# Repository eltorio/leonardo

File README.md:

# Leonardo
Arduino Leonardo schematic ported to Kicad

# Star the project

**If you appreciate my work, please consider giving it a star! 🤩**

# Kicad 8
The design has been ported to Kicad 8.  
* DRC shows no error nor warning on PCB.
* All selected parts are easily availables.
* All parts contains 3 additional fields
    * Manufacturer containing the name of the manufacturer
    * Manufacturer_ref containing the part real reference
    * Digikey_ref containing a Digikey part number

NM, DNP parts are parts not mounted

# Why
Because I need to adapt the Leonardo design to include other functionalities my first work is to port the very good Arduino Leonardo rev3d to Kicad 6.  

# Crystal
16MHz Crystal is not yet selected…

# Schematic

# Board

The board is adapted and routed with the parts I have selected.  
Kicad 8 DRC check doesn't show any errors nor any warning.  
Component references are hidden by default to match the Arduino Leonardo silkscreen. If you need the references, use the [Hide References plugin](https://github.com/joelsa/kicad-hide-references-plugin) which can be easily installed via the Plugin and Content Manager.

# 3D Render

## Without component references

## With component references

# BOM
The [BOM](https://raw.githubusercontent.com/eltorio/leonardo/main/Leonardo_Rev3e.html) was automatically generated with [python/bom.py](https://github.com/eltorio/leonardo/blob/main/python/bom.py) add this script in the BOM dialog.  
The html BOM was converted to MarkDown with https://www.convertsimple.com/convert-html-to-markdown/   

[comment]: <> (generated from html bom with https://www.convertsimple.com/convert-html-to-markdown/)  
**Component Count: 56**

| Ref | Qnty | Value | Footprint | Datasheet | Manufacturer | Manufacturer_ref | Digikey_ref |
| --- | --- | --- | --- | --- | --- | --- | --- |
| C1, C2, C6, C9, C13, C22 | 6   | 100n | Leonardo_Rev3e:C0603-ROUND | [link](https://connect.kemet.com:7667/gateway/IntelliData-ComponentDocumentation/1.0/download/datasheet/C0603C104J4RACTU) | Kemet | C0603C104J4RAC7867 | [399-C0603C104J4RAC7867CT-ND](https://www.digikey.com/en/products?mpart=399-C0603C104J4RAC7867CT-ND) |
| C3, C4 | 2   | 22p | Leonardo_Rev3e:C0603-ROUND | [link](https://connect.kemet.com:7667/gateway/IntelliData-ComponentDocumentation/1.0/download/datasheet/C0603C220K5RAC7867) | Kemet | C0603C220K5RAC7867 | [399-14962-1-ND](https://www.digikey.com/en/products?mpart=399-14962-1-ND) |
| C5, C7, C11, C14 | 4   | 1uF | Leonardo_Rev3e:C0603-ROUND | [link](https://connect.kemet.com:7667/gateway/IntelliData-ComponentDocumentation/1.0/download/datasheet/C0603C105K4RAC7411) | Kemet | C0603C105K4RAC7411 | [399-C0603C105K4RAC7411CT-ND](https://www.digikey.com/en/products?mpart=399-C0603C105K4RAC7411CT-ND) |
| C8, C10, C12 | 3   | 10u | Leonardo\_Rev3d:SMC\_B | [link](https://api.kemet.com/component-edge/download/datasheet/T491B106M016AT.pdf) | Kemet | T491B106M016AT | [399-3708-1-ND](https://www.digikey.com/en/products?mpart=399-3708-1-ND) |
| D1  | 1   | M7  | Leonardo_Rev3e:SMB |     |     |     |     |
| D2  | 1   | 1N4148W-TP | Leonardo_Rev3e:MINIMELF | [link](https://www.mccsemi.com/pdf/Products/1N4148W(SOD-123).pdf) | MCC | 1N4148W-TP | [1N4148WTPMSCT-ND](https://www.digikey.com/en/products?mpart=1N4148WTPMSCT-ND) |
| D+0 | 1   | DNP | Leonardo_Rev3e:TP-1.00MM |     |     |     |     |
| D-0 | 1   | DNP | Leonardo_Rev3e:TP-1.00MM |     |     |     |     |
| EXTPOWER0 | 1   | POWERSUPPLY_DC21MMX | Leonardo\_Rev3d:POWERSUPPLY\_DC-21MM |     |     |     |     |
| F1  | 1   | MF-MSMF050-2 500mA | Leonardo_Rev3e:L1812 | [link](https://www.bourns.com/docs/product-datasheets/mf-msmf.pdf) | Bourns | MF-MSMF050-2 | [MF-MSMF050-2CT-ND](https://www.digikey.com/en/products?mpart=MF-MSMF050-2CT-ND) |
| FID1, FID2, FID3 | 3   | DNP | Leonardo_Rev3e:FD-1-1.5 |     |     |     |     |
| GND0 | 1   | DNP | Leonardo_Rev3e:TP-1.00MM |     |     |     |     |
| IC1 | 1   | REG1117-5 | Leonardo_Rev3e:SOT223 | [link](https://www.ti.com/lit/gpn/reg1117) | TI  | REG1117-5 | [REG1117-5-ND](https://www.digikey.com/en/products?mpart=REG1117-5-ND) |
| IC2 | 1   | LMV358IDGKR | Leonardo_Rev3e:MSOP08 | [link](https://www.ti.com/lit/gpn/lmv358) | TI  | 296-13455-1-ND | [LMV358IDGKR](https://www.digikey.com/en/products?mpart=LMV358IDGKR) |
| ICSP0 | 1   | ICSP | Leonardo_Rev3e:2X03 | [link](https://www.te.com/commerce/DocumentDelivery/DDEController?Action=srchrtrv&DocNm=146486&DocType=Customer+Drawing&DocLang=English) | TE  | 5-146486-3 | [A128860-ND](https://www.digikey.com/en/products?mpart=A128860-ND) |
| J1  | 1   | USBMICRO | Leonardo_Rev3e:10118194-0001LF | [link](https://www.amphenol-cs.com/media/wysiwyg/files/drawing/10118194.pdf) | Amphenol | 10118194-0001LF | [609-4618-1-ND](https://www.digikey.com/en/products?mpart=609-4618-1-ND) |
| J2, J3 | 2   | 8x1F-H8.5 | Leonardo_Rev3e:1X08 | [link](https://media.digikey.com/pdf/Data%20Sheets/Sullins%20PDFs/Female_Headers.100_DS.pdf) | Sullins | PPPC081LFBN-RC | [S7041-ND](https://www.digikey.com/en/products?mpart=S7041-ND) |
| J4  | 1   | 6x1F-H8.5 | Leonardo_Rev3e:1X06 | [link](https://media.digikey.com/pdf/Data%20Sheets/Sullins%20PDFs/Female_Headers.100_DS.pdf) | Sullins | PPPC061LFBN-RC | [S7039-ND](https://www.digikey.com/en/products?mpart=S7039-ND) |
| JP1 | 1   | 10x1F-H8.5 | Leonardo_Rev3e:1X10 | [link](https://media.digikey.com/pdf/Data%20Sheets/Sullins%20PDFs/Female_Headers.100_DS.pdf) | Sullins | PPPC101LFBN-RC | [S7043-ND](https://www.digikey.com/en/products?mpart=S7043-ND) |
| JP2 | 1   | OTG | Leonardo\_Rev3d:HEADER\_2_2.54 | [link](~) | Samtex | DW-02-07-T-S-200 | [SAM15134-ND](https://www.digikey.com/en/products?mpart=SAM15134-ND) |
| L0  | 1   | Yellow | Leonardo\_Rev3d:CHIPLED\_0805 | [link](https://optoelectronics.liteon.com/upload/download/DS22-2000-110/LTST-C171KSKT.pdf) | Lite-on | LTST-C171KSKT | [160-1428-1-ND](https://www.digikey.com/en/products?mpart=160-1428-1-ND) |
| L1, L2 | 2   | MH2029-300Y | Leonardo_Rev3e:0805 | [link](https://www.bourns.com/docs/Product-Datasheets/mh.pdf) | Bourns | MH2029-300Y | [MH2029-300YCT-ND](https://www.digikey.com/en/products?mpart=MH2029-300YCT-ND) |
| ON0 | 1   | Green | Leonardo\_Rev3d:CHIPLED\_0805 | [link](https://optoelectronics.liteon.com/upload/download/DS22-2000-110/LTST-C171KSKT.pdf) | Lite-on | LTST-C171KGKT | [160-1426-1-ND](https://www.digikey.com/en/products?mpart=160-1426-1-ND) |
| R1  | 1   | 1M  | Leonardo_Rev3e:R0603-ROUND | [link](https://www.bourns.com/docs/product-datasheets/cr.pdf?sfvrsn=574d41f6_14) | Bourns | CR0603-FX-1004ELF | [CR0603-FX-1004ELFCT-ND](https://www.digikey.com/en/products?mpart=CR0603-FX-1004ELFCT-ND) |
| R2, R3 | 2   | NM  | Leonardo_Rev3e:R0402 |     |     |     |     |
| R4  | 1   | 10K | Leonardo_Rev3e:R0603-ROUND | [link](https://www.bourns.com/docs/product-datasheets/cr.pdf?sfvrsn=574d41f6_14) | Bourns | CR0603-FX-1002ELF | [CR0603-FX-1002ELFCT-ND](https://www.digikey.com/en/products?mpart=CR0603-FX-1002ELFCT-ND) |
| RESET0 | 1   | TS07-667-30-BK-160-SMT-TR | Leonardo_Rev3e:TS07 | [link](https://www.cuidevices.com/product/resource/ts07.pdf) | CUI | TS07-667-30-BK-160-SMT-TR | [2223-TS07-667-30-BK-160-SMT-TRCT-ND](https://www.digikey.com/en/products?mpart=2223-TS07-667-30-BK-160-SMT-TRCT-ND) |
| RN1 | 1   | 10K | Leonardo_Rev3e:CAY16 | [link](https://www.bourns.com/docs/Product-Datasheets/CATCAY.pdf) | Bourns | CAY16-1002F4LF | [CAY16-1002F4LFCT-ND](https://www.digikey.com/en/products?mpart=CAY16-1002F4LFCT-ND) |
| RN2 | 1   | 1K  | Leonardo_Rev3e:CAY16 | [link](https://www.bourns.com/docs/Product-Datasheets/CATCAY.pdf) | Bourns | CAY16-1001F4LF | [CAY16-1001F4LFCT-ND](https://www.digikey.com/en/products?mpart=CAY16-1001F4LFCT-ND) |
| RN3 | 1   | 22R | Leonardo_Rev3e:CAY16 | [link](https://www.bourns.com/docs/Product-Datasheets/CATCAY.pdf) | Bourns | CAY16-22R0F4LF | [CAY16-22R0F4LFCT-ND](https://www.digikey.com/en/products?mpart=CAY16-22R0F4LFCT-ND) |
| RX0 | 1   | Yellow | Leonardo\_Rev3d:CHIPLED\_0805 | [link](https://optoelectronics.liteon.com/upload/download/DS22-2000-110/LTST-C171KSKT.pdf) | Lite-on | LTST-C171KSKT | [160-1426-1-ND](https://www.digikey.com/en/products?mpart=160-1426-1-ND) |
| T1  | 1   | FDN340P | Leonardo_Rev3e:SOT-23 | [link](https://media.digikey.com/pdf/Data%20Sheets/UTD%20Semi%20PDFs/UMW%20FDN340P.pdf) | UMW | FDN340P | [4518-FDN340PCT-ND](https://www.digikey.com/en/products?mpart=4518-FDN340PCT-ND) |
| TX0 | 1   | Yellow | Leonardo\_Rev3d:CHIPLED\_0805 | [link](https://optoelectronics.liteon.com/upload/download/DS22-2000-110/LTST-C171KSKT.pdf) | Lite-on | LTST-C171KSKT | [160-1426-1-ND](https://www.digikey.com/en/products?mpart=160-1426-1-ND) |
| U1  | 1   | ATMEGA32U4-XUMU | Leonardo_Rev3e:QFN44ML7X7 | [link](http://ww1.microchip.com/downloads/en/DeviceDoc/Atmel-7766-8-bit-AVR-ATmega16U4-32U4_Summary.pdf) | Microchip | ATMEGA32U4-MU | [ATMEGA32U4-MU-ND](https://www.digikey.com/en/products?mpart=ATMEGA32U4-MU-ND) |
| U2  | 1   | ATMEGA32U4-XUAU | Leonardo_Rev3e:TQFP44-PAD | [link](http://ww1.microchip.com/downloads/en/DeviceDoc/Atmel-7766-8-bit-AVR-ATmega16U4-32U4_Summary.pdf) | Microchip | ATMEGA32U4-AU | [ATMEGA32U4-AU-ND](https://www.digikey.com/en/products?mpart=ATMEGA32U4-AU-ND) |
| U3  | 1   | LP2985-33DBVR | Leonardo_Rev3e:SOT23-DBV | [link](https://www.ti.com/lit/gpn/LP2985-N) | TI  | LP2985IM5-3.3 | [LP2985IM5-3.3CT-ND](https://www.digikey.com/en/products?mpart=LP2985IM5-3.3CT-ND) |
| VUSB0 | 1   | DNP | Leonardo_Rev3e:TP-1.00MM |     |     |     |     |
| Y1  | 1   | 16MHz KX-7 | Leonardo_Rev3e:CRYSTAL-3.2-2.5 |     |     |     |     |
| Z1, Z2 | 2   | CG0603MLC-05E | Leonardo\_Rev3d:CT\_CN0603 | [link](https://www.bourns.com/docs/product-datasheets/cga-mlc.pdf) | Bourns | CG0603MLC-05E | [CG0603MLC-05ECT-ND](https://www.digikey.com/en/products?mpart=CG0603MLC-05ECT-ND) |

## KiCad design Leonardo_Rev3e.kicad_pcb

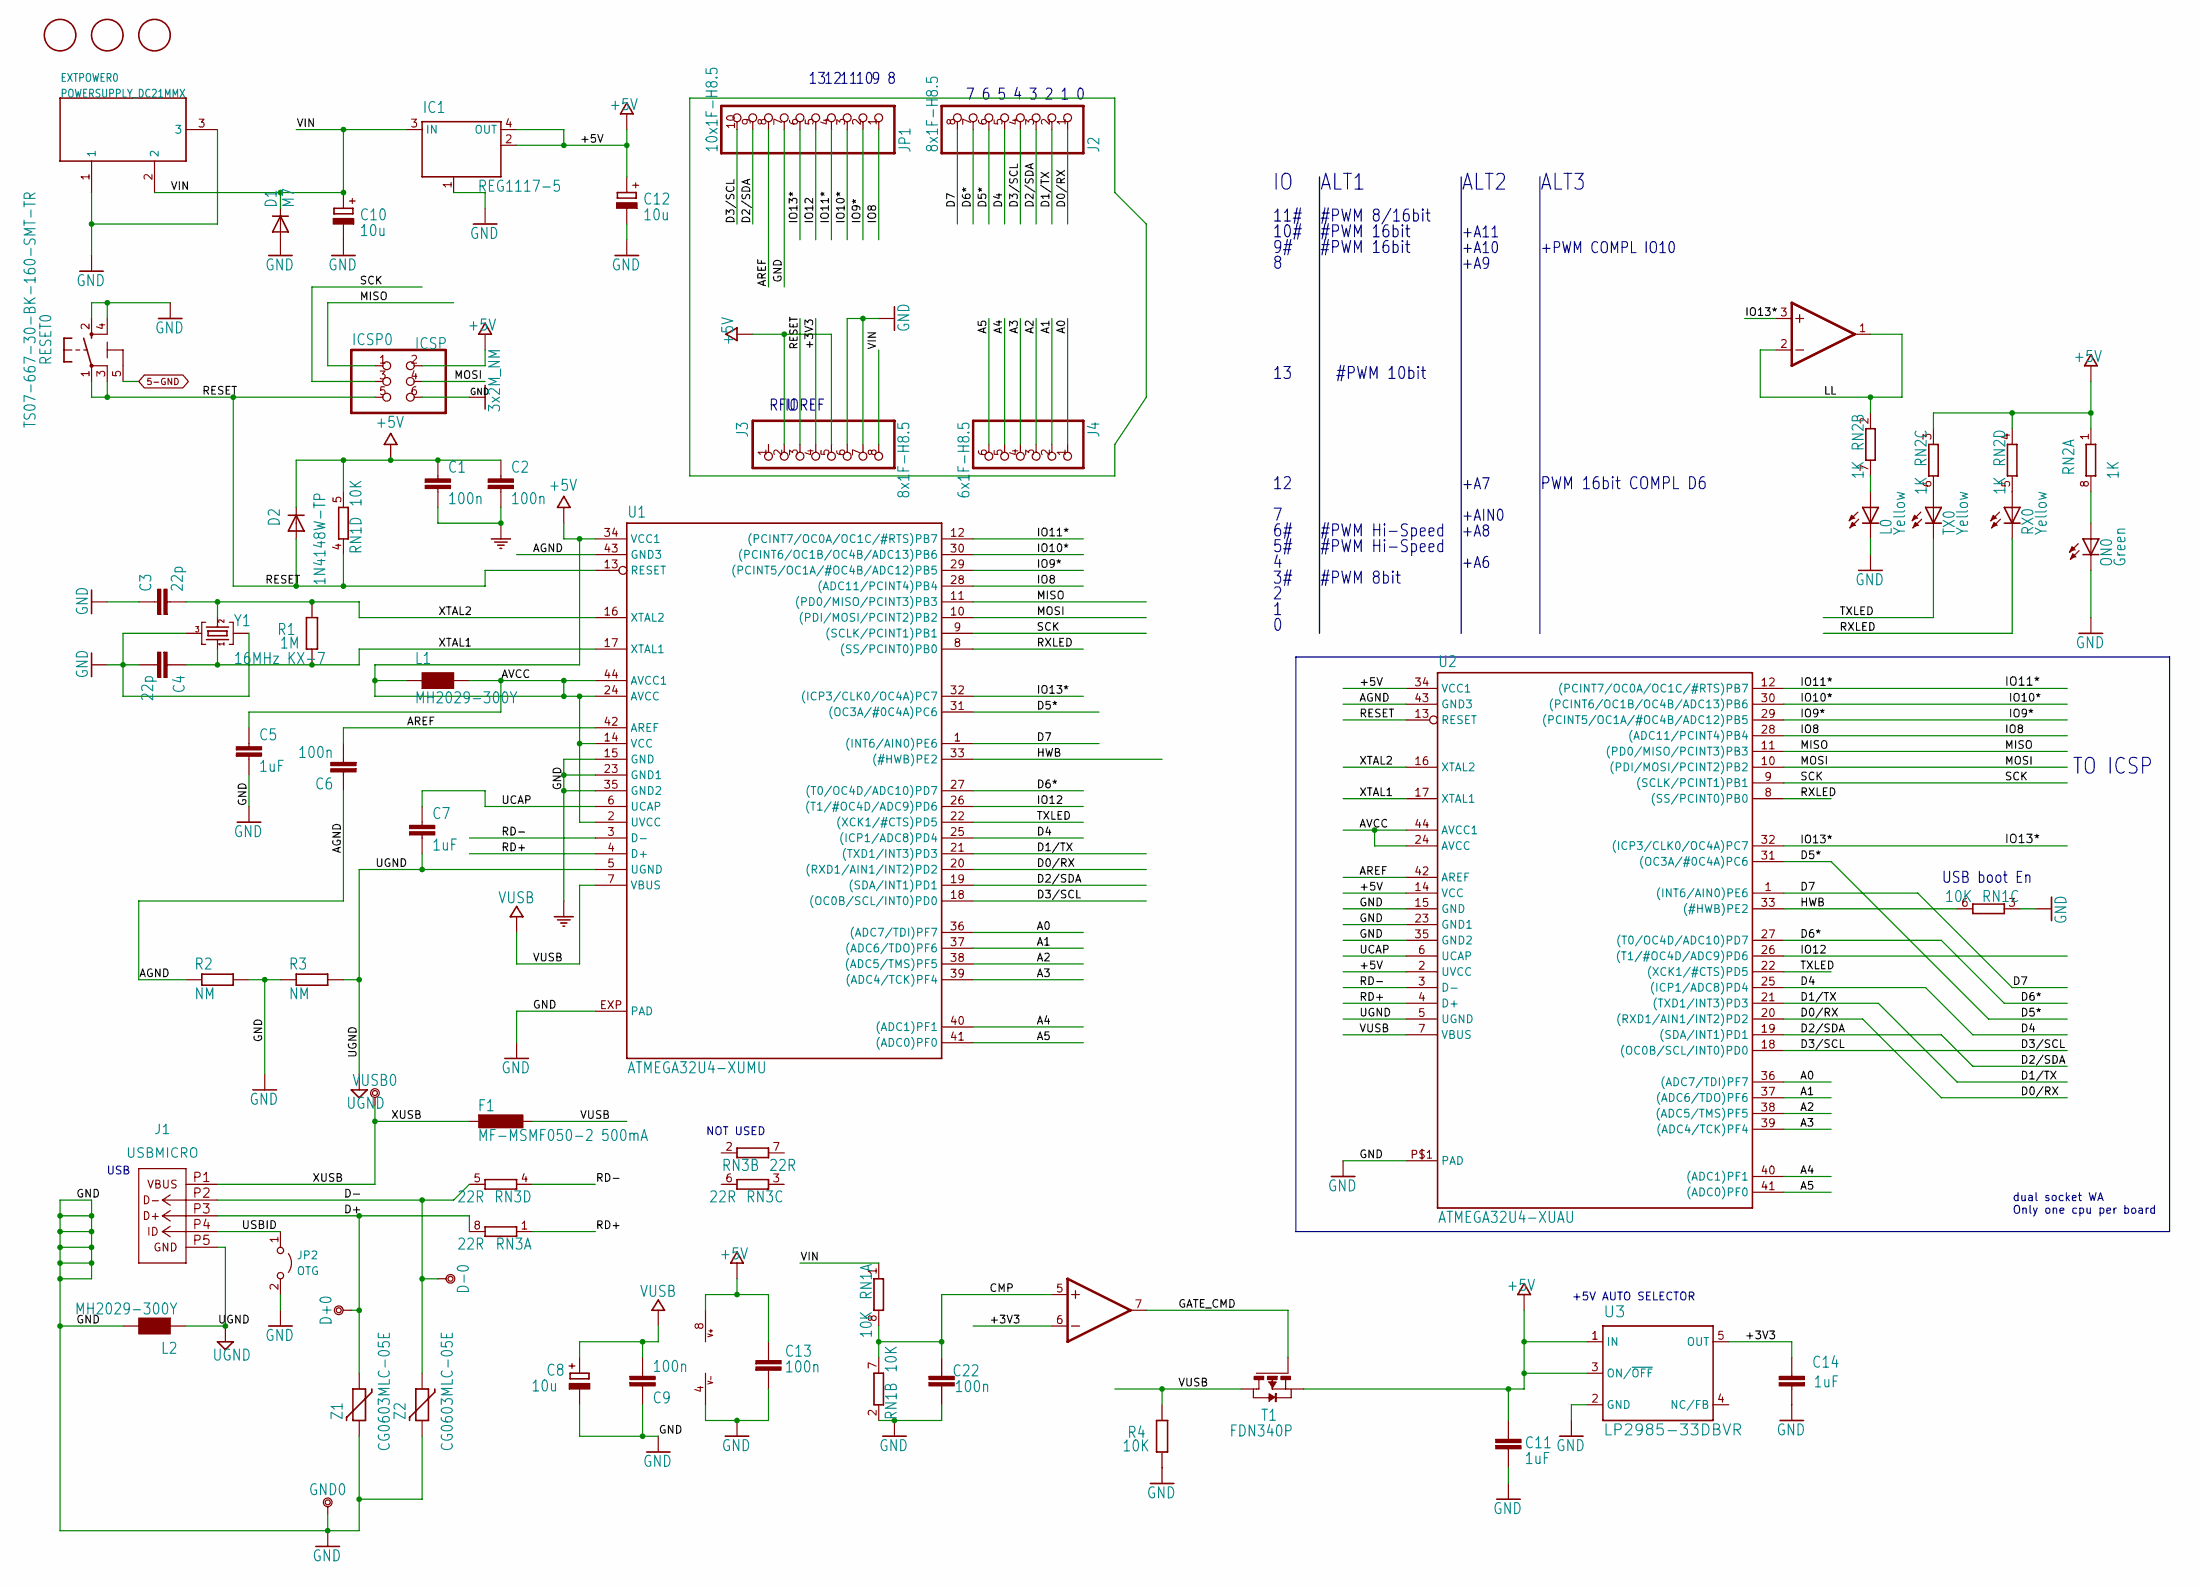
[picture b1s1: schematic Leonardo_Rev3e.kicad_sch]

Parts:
C1, C2, C6, C9, C13, C22: 100n; C0603-ROUND; Digikey_ref 399-C0603C104J4RAC7867CT-ND
C3, C4: 22p; C0603-ROUND; Digikey_ref 399-14962-1-ND
C5, C7, C11, C14: 1uF; C0603-ROUND; Digikey_ref 399-C0603C105K4RAC7411CT-ND
C8, C10, C12: 10u; SMC_B; Digikey_ref 399-3708-1-ND
D1: M7; SMB
D2: 1N4148W-TP; MINIMELF; Digikey_ref 1N4148WTPMSCT-ND
D+0: DNP; TP-1.00MM
D-0: DNP; TP-1.00MM
EXTPOWER0: POWERSUPPLY_DC21MMX; POWERSUPPLY_DC-21MM
F1: MF-MSMF050-2 500mA; L1812; Digikey_ref MF-MSMF050-2CT-ND
FID1, FID2, FID3: DNP; FD-1-1.5
GND0: DNP; TP-1.00MM
IC1: REG1117-5; SOT223; Digikey_ref REG1117-5-ND
IC2: LMV358IDGKR; MSOP08; Digikey_ref LMV358IDGKR
ICSP0: ICSP; 2X03; Digikey_ref A128860-ND
J1: USBMICRO; 10118194-0001LF; Digikey_ref 609-4618-1-ND
J2, J3: 8x1F-H8.5; 1X08; Digikey_ref S7041-ND
J4: 6x1F-H8.5; 1X06; Digikey_ref S7039-ND
JP1: 10x1F-H8.5; 1X10; Digikey_ref S7043-ND
JP2: OTG; HEADER_2_2.54; Digikey_ref SAM15134-ND
L0: Yellow; CHIPLED_0805; Digikey_ref 160-1428-1-ND
L1, L2: MH2029-300Y; 0805; Digikey_ref MH2029-300YCT-ND
ON0: Green; CHIPLED_0805; Digikey_ref 160-1426-1-ND
R1: 1M; R0603-ROUND; Digikey_ref CR0603-FX-1004ELFCT-ND
R2, R3: NM; R0402
R4: 10K; R0603-ROUND; Digikey_ref CR0603-FX-1002ELFCT-ND
RESET0: TS07-667-30-BK-160-SMT-TR; TS07; Digikey_ref 2223-TS07-667-30-BK-160-SMT-TRCT-ND
RN1: 10K; CAY16; Digikey_ref CAY16-1002F4LFCT-ND
RN2: 1K; CAY16; Digikey_ref CAY16-1001F4LFCT-ND
RN3: 22R; CAY16; Digikey_ref CAY16-22R0F4LFCT-ND
RX0: Yellow; CHIPLED_0805; Digikey_ref 160-1426-1-ND
T1: FDN340P; SOT-23; Digikey_ref 4518-FDN340PCT-ND
TX0: Yellow; CHIPLED_0805; Digikey_ref 160-1426-1-ND
U1: ATMEGA32U4-XUMU; QFN44ML7X7; Digikey_ref ATMEGA32U4-MU-ND
U2: ATMEGA32U4-XUAU; TQFP44-PAD; Digikey_ref ATMEGA32U4-AU-ND
U3: LP2985-33DBVR; SOT23-DBV; Digikey_ref LP2985IM5-3.3CT-ND
VUSB0: DNP; TP-1.00MM
Y1: 16MHz KX-7; CRYSTAL-3.2-2.5
Z1, Z2: CG0603MLC-05E; CT_CN0603; Digikey_ref CG0603MLC-05ECT-ND

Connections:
3x2M_NM: C1.2, C2.2, C3.1, C4.2, C5.2, C8.-, C9.1, C10.-, C11.1, C12.-, C13.2, C14.1, C22.1, D1.A, EXTPOWER0.1, EXTPOWER0.3, GND0.X, IC1.1 (GND/ADJ), IC2.4 (V-), ICSP0.6, J3.6, J3.7, JP1.7, JP2.2 (B), L0.C, L2.2, ON0.C, R2.2, R3.1, R4.1, RESET0.2, RESET0.4, RN1.2 (1), RN1.3 (1), U1.15 (GND), U1.23 (GND1), U1.35 (GND2), U1.EXP (PAD), U2.15 (GND), U2.23 (GND1), U2.35 (GND2), U2.P$1 (PAD), U3.2 (GND), Y1.2 (GND@1), Y1.4 (GND@2), Z1.2, Z2.2
5-GND: RESET0.5 (5-GND)
+5V: C1.1, C2.1, C5.1, C11.2, C12.+, C13.1, D2.C, IC1.2 (OUT@1), IC1.4 (OUT), IC2.8 (V+), ICSP0.2, J3.2, J3.5, L1.1, L1.2, RN1.5 (2), RN2.1, RN2.3 (1), RN2.4 (1), T1.2 (S), U1.2 (UVCC), U1.14 (VCC), U1.24 (AVCC), U1.34 (VCC1), U1.44 (AVCC1), U2.2 (UVCC), U2.14 (VCC), U2.24 (AVCC), U2.34 (VCC1), U2.44 (AVCC1), U3.1 (IN), U3.3 (ON/~OFF)
/+3V3: C14.2, IC2.6 (-IN), J3.4, U3.5 (OUT)
/A0: J4.1, U1.36 ((ADC7/TDI)PF7), U2.36 ((ADC7/TDI)PF7)
/A1: J4.2, U1.37 ((ADC6/TDO)PF6), U2.37 ((ADC6/TDO)PF6)
/A2: J4.3, U1.38 ((ADC5/TMS)PF5), U2.38 ((ADC5/TMS)PF5)
/A3: J4.4, U1.39 ((ADC4/TCK)PF4), U2.39 ((ADC4/TCK)PF4)
/A4: J4.5, U1.40 ((ADC1)PF1), U2.40 ((ADC1)PF1)
/A5: J4.6, U1.41 ((ADC0)PF0), U2.41 ((ADC0)PF0)
/AGND: C6.1, R2.1, U1.43 (GND3), U2.43 (GND3)
/AREF: C6.2, JP1.8, U1.42 (AREF), U2.42 (AREF)
/CMP: C22.2, IC2.5 (+IN), RN1.7 (2), RN1.8 (2)
/D0/RX: J2.1, U1.20 ((RXD1/AIN1/INT2)PD2), U2.20 ((RXD1/AIN1/INT2)PD2)
/D1/TX: J2.2, U1.21 ((TXD1/INT3)PD3), U2.21 ((TXD1/INT3)PD3)
/D2/SDA: J2.3, JP1.9, U1.19 ((SDA/INT1)PD1), U2.19 ((SDA/INT1)PD1)
/D3/SCL: J2.4, JP1.10, U1.18 ((OC0B/SCL/INT0)PD0), U2.18 ((OC0B/SCL/INT0)PD0)
/D4: J2.5, U1.25 ((ICP1/ADC8)PD4), U2.25 ((ICP1/ADC8)PD4)
/D5*: J2.6, U1.31 ((OC3A/#0C4A)PC6), U2.31 ((OC3A/#0C4A)PC6)
/D6*: J2.7, U1.27 ((T0/OC4D/ADC10)PD7), U2.27 ((T0/OC4D/ADC10)PD7)
/D7: J2.8, U1.1 ((INT6/AIN0)PE6), U2.1 ((INT6/AIN0)PE6)
/D+: D+0.X, J1.P3 (D+), RN3.8 (2), Z1.1
/D-: D-0.X, J1.P2 (D-), RN3.5 (2), Z2.1
/GATE_CMD: IC2.7 (OUT), T1.3 (G)
/HWB: RN1.6 (2), U1.33 ((#HWB)PE2), U2.33 ((#HWB)PE2)
/IO8: JP1.1, U1.28 ((ADC11/PCINT4)PB4), U2.28 ((ADC11/PCINT4)PB4)
/IO9*: JP1.2, U1.29 ((PCINT5/OC1A/#OC4B/ADC12)PB5), U2.29 ((PCINT5/OC1A/#OC4B/ADC12)PB5)
/IO10*: JP1.3, U1.30 ((PCINT6/OC1B/OC4B/ADC13)PB6), U2.30 ((PCINT6/OC1B/OC4B/ADC13)PB6)
/IO11*: JP1.4, U1.12 ((PCINT7/OC0A/OC1C/#RTS)PB7), U2.12 ((PCINT7/OC0A/OC1C/#RTS)PB7)
/IO12: JP1.5, U1.26 ((T1/#OC4D/ADC9)PD6), U2.26 ((T1/#OC4D/ADC9)PD6)
/IO13*: IC2.3 (+IN), JP1.6, U1.32 ((ICP3/CLK0/OC4A)PC7), U2.32 ((ICP3/CLK0/OC4A)PC7)
/LL: IC2.1 (OUT), IC2.2 (-IN), RN2.2 (1)
/MISO: ICSP0.1, U1.11 ((PD0/MISO/PCINT3)PB3), U2.11 ((PD0/MISO/PCINT3)PB3)
/MOSI: ICSP0.4, U1.10 ((PDI/MOSI/PCINT2)PB2), U2.10 ((PDI/MOSI/PCINT2)PB2)
/RD+: RN3.1, U1.4 (D+), U2.4 (D+)
/RD-: RN3.4 (1), U1.3 (D-), U2.3 (D-)
/RESET: D2.A, ICSP0.5, J3.3, RESET0.1, RESET0.3, RN1.4 (1), U1.13 (RESET), U2.13 (RESET)
/RXLED: RX0.C, U1.8 ((SS/PCINT0)PB0), U2.8 ((SS/PCINT0)PB0)
/SCK: ICSP0.3, U1.9 ((SCLK/PCINT1)PB1), U2.9 ((SCLK/PCINT1)PB1)
/TXLED: TX0.C, U1.22 ((XCK1/#CTS)PD5), U2.22 ((XCK1/#CTS)PD5)
/UCAP: C7.1, U1.6 (UCAP), U2.6 (UCAP)
/USBID: J1.P4 (ID), JP2.1 (A)
/VIN: C10.+, D1.C, EXTPOWER0.2, IC1.3 (IN), J3.8, RN1.1
/XTAL1: C4.1, R1.1, U1.17 (XTAL1), U2.17 (XTAL1), Y1.1 (C1)
/XTAL2: C3.2, R1.2, U1.16 (XTAL2), U2.16 (XTAL2), Y1.3 (C2)
/XUSB: F1.2, J1.P1 (VBUS), VUSB0.X
unnamed: ON0.A, RN2.8 (2)
unnamed: L0.A, RN2.7 (2)
unnamed: RN2.6 (2), TX0.A
unnamed: RN2.5 (2), RX0.A
UGND: C7.2, J1.P5 (GND), L2.1, R3.2, U1.5 (UGND), U2.5 (UGND)
VUSB: C8.+, C9.2, F1.1, R4.2, T1.1 (D), U1.7 (VBUS), U2.7 (VBUS)

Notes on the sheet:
#PWM 8/16bit
PWM 16bit COMPL D6
USB boot En
NOT USED
RFU
#PWM 8bit
+PWM COMPL IO10
#PWM 16bit
TO ICSP
dual socket WA Only one cpu per board
#PWM Hi-Speed
+A10
11#
IOREF
+5V AUTO SELECTOR
+AIN0
ALT3
+A8
+A9
ALT1
+A6
#PWM 10bit
USB
ALT2
10#
+A11
+A7

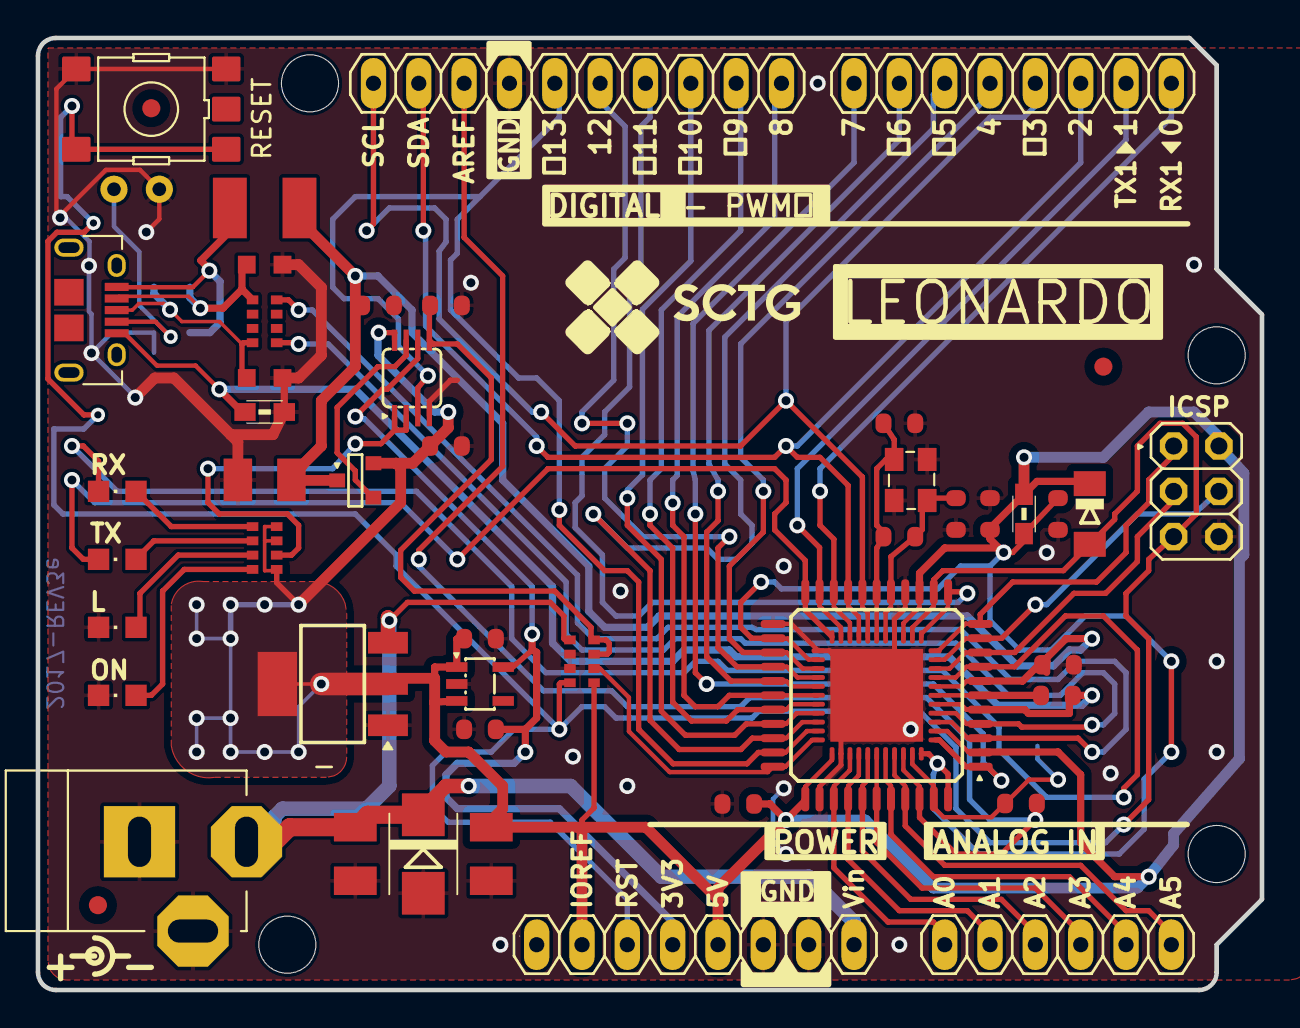
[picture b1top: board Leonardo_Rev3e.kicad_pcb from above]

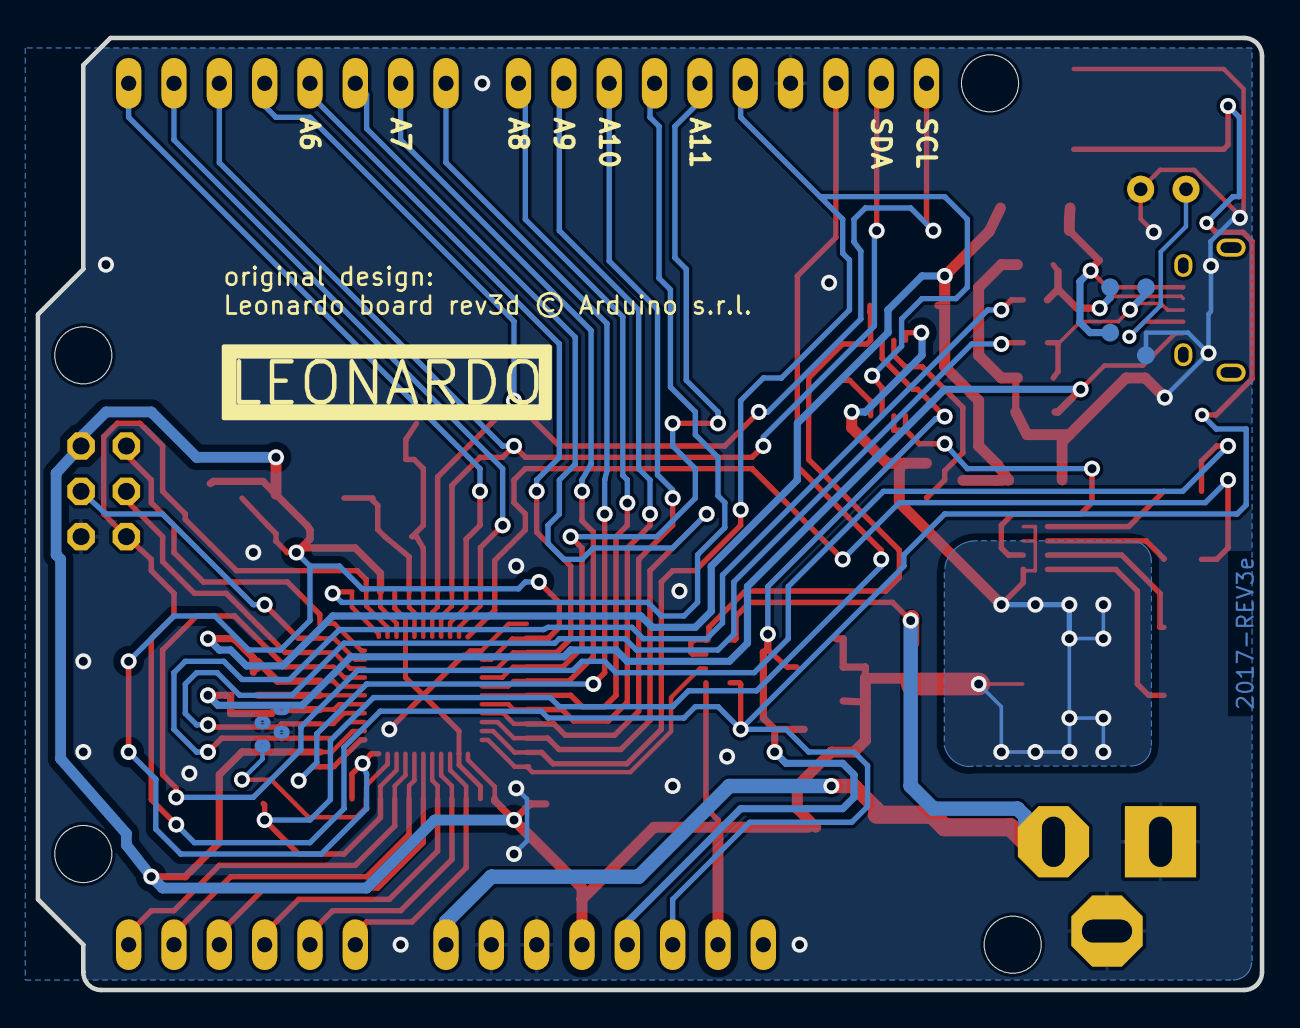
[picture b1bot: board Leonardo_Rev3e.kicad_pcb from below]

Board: 2 copper layers, 68.6 x 53.3 mm, 60 parts (2 on the bottom side), 51 nets.

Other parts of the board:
@HOLE0, @HOLE1, @HOLE2, @HOLE3: (no value)

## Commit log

2023-01-08 update version
2023-01-08 add fabrication
2023-01-08 Update documentation
2023-01-08 put schematic
2023-01-08 update image
2023-01-08 Add license
2023-01-08 update doc
2023-01-08 add link to schematic
2023-02-27 BUG: Correct D7/HWB error and upgrade to Kicad 7
2024-12-17 chore: port to kicad 8
2024-12-17 feat: resize all references/text and match pin markings
2024-12-17 chore: clean up footprint library
2024-12-17 fix: move user comments to correct layer
2024-12-17 feat: add labels to match original design
2024-12-17 chore: clean up footprints and layout
2024-12-17 chore: update .gitignore
2024-12-17 chore: pass drc checks
2024-12-17 chore: update board.png
2024-12-17 chore: clean up layout
2024-12-17 feat: add 3d rendered images
2024-12-17 chore: update 3d renders
2024-12-17 fix: correct QFN44ML7X7 footprint
2024-12-17 chore: update README.md
2024-12-17 feat: add 3d models
2024-12-17 chore: regenerate fabrication files
2024-12-17 Fix README.md broken links
2024-12-17 Thanks to aanas-sayed

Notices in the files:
Leonardo_Rev3e.kicad_pcb:
Leonardo board rev3d © Arduino s.r.l.
parts and their libraries:
©Arduino s.r.l / Ronan LE MEILLAT
Copyright 2021 Accelerated Designs. All rights reserved.
